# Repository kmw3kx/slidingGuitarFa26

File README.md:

# slidingGuitarFa26
Repo for all of the electronics &amp; code for my Fa26 capstone group 

## Daisy Pins

## Basic idea

6 string guitar with glass slider attached to linear actuator.

From gemini:

$$\text{Total Encoder Positions} = \frac{575\text{ mm}}{0.1894\text{ mm/count}} \approx \mathbf{3,036\text{ discrete positions}}$$

My original idea was to use pitchbend midi control for slider position, but it doesn't appear to be completely necessary. But it will fit for now.

Then I will use a cc channel or 2 for the gains on the Op-amps

I will build this demo in puredata so that I can start composing for it.

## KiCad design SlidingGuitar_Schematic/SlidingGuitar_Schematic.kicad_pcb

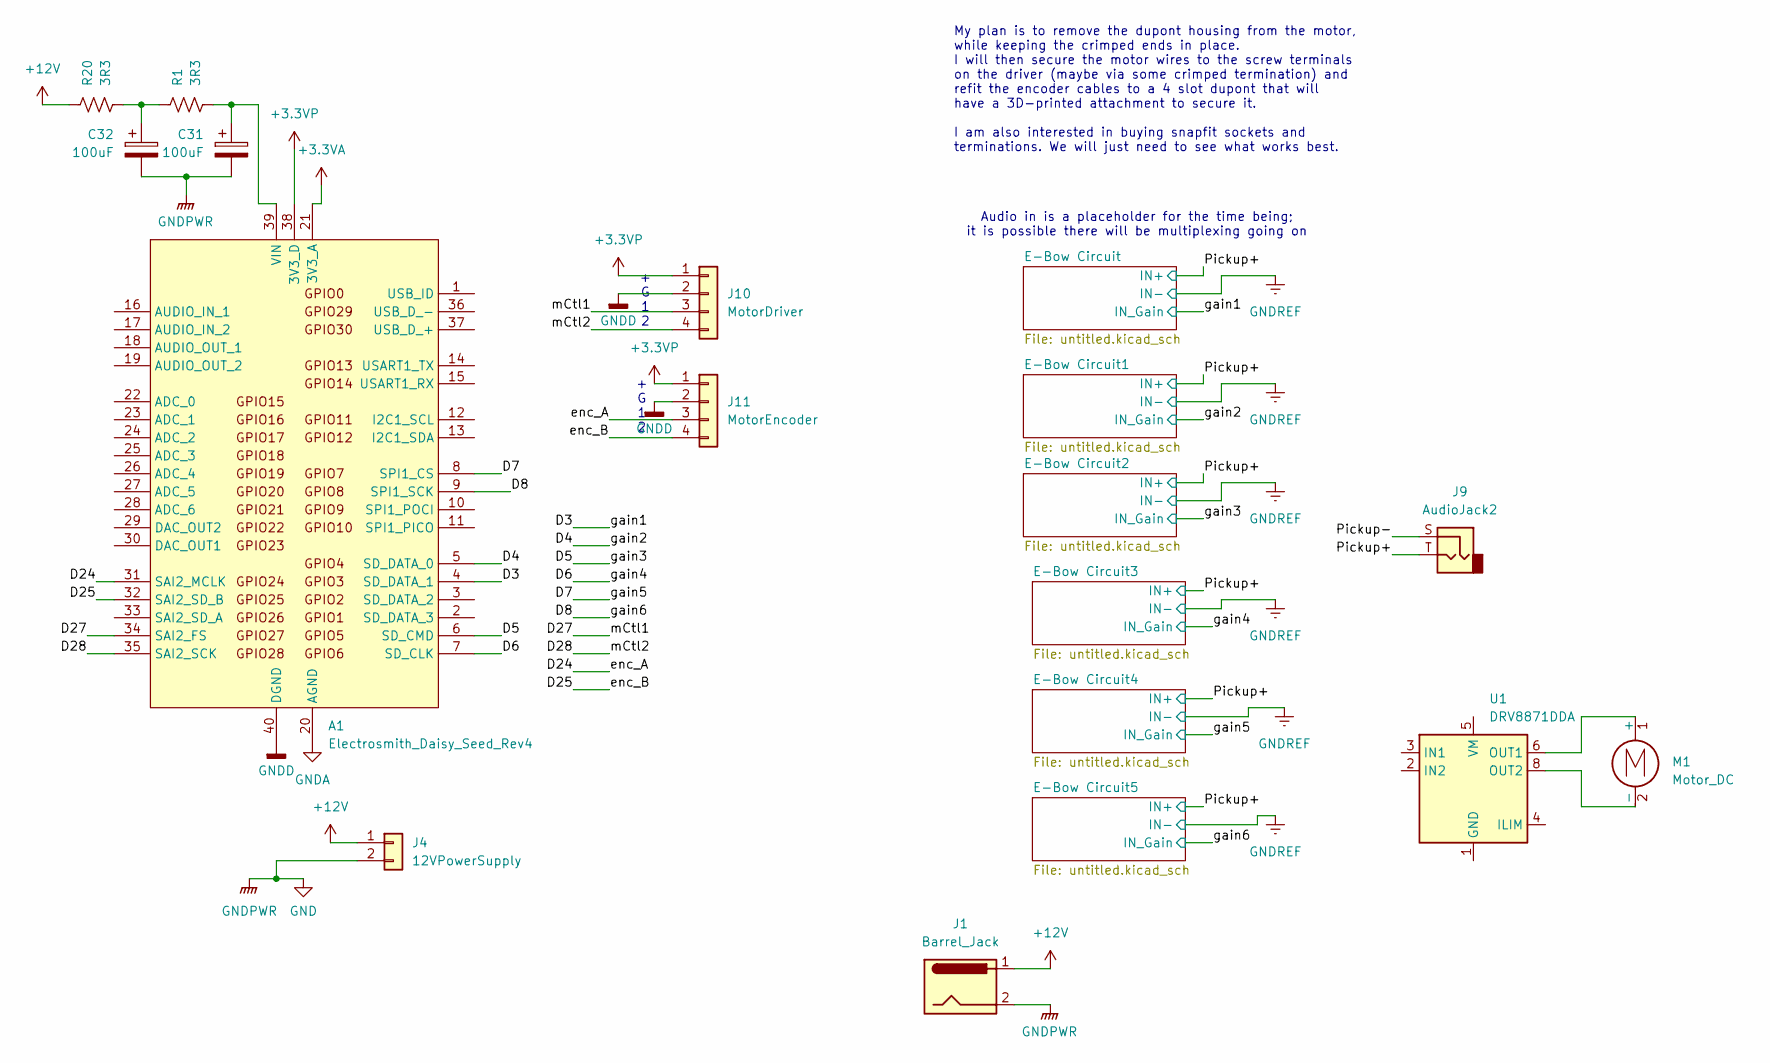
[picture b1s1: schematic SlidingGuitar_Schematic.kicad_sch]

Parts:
A1: Electrosmith_Daisy_Seed_Rev4; Electrosmith_Daisy_Seed
C31, C32: 100uF; CP_Radial_D8.0mm_P5.00mm
J1: Barrel_Jack; BarrelJack_Horizontal
J4: 12VPowerSupply; PinHeader_1x02_P2.54mm_Vertical
J9: AudioJack2
J10: MotorDriver; PinHeader_1x04_P2.54mm_Vertical
J11: MotorEncoder; PinHeader_1x04_P2.54mm_Vertical
M1: Motor_DC
R1, R20: 3R3; R_Axial_DIN0207_L6.3mm_D2.5mm_P7.62mm_Horizontal
U1: DRV8871DDA; Texas_HTSOP-8-1EP_3.9x4.9mm_P1.27mm_EP2.95x4.9mm_Mask2.4x3.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

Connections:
+3.3VA: A1.21 (3V3_A)
+3.3VP: A1.38 (3V3_D), J10.1, J11.1
+12V: J1.1, J4.1, R20.1; also elsewhere on the board
/D3: A1.4 (SD_DATA_1); also elsewhere on the board
/D4: A1.5 (SD_DATA_0); also elsewhere on the board
/D5: A1.6 (SD_CMD); also elsewhere on the board
/D6: A1.7 (SD_CLK); also elsewhere on the board
/D7: A1.8 (SPI1_CS); also elsewhere on the board
/D8: A1.9 (SPI1_SCK); also elsewhere on the board
/D24: A1.31 (SAI2_MCLK), J11.3
/D25: A1.32 (SAI2_SD_B), J11.4
/D27: A1.34 (SAI2_FS), J10.3
/D28: A1.35 (SAI2_SCK), J10.4
GND: C31.2, C32.2, J1.2, J4.2; also elsewhere on the board
GNDA: A1.20 (AGND)
GNDD: A1.40 (DGND), J10.2, J11.2; also elsewhere on the board
unnamed: A1.39 (VIN), C31.1, R1.2
unnamed: C32.1, R1.1, R20.2
unnamed: M1.1 (+), U1.6 (OUT1)
unnamed: M1.2 (-), U1.8 (OUT2)
unnamed: U1.1 (GND), U1.7 (GND), U1.9 (GND)

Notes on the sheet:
+ G 1 2
Audio in is a placeholder for the time being; it is possible there will be multiplexing going on
My plan is to remove the dupont housing from the motor, while keeping the crimped ends in place. I will then secure the motor wires to the screw terminals on the driver (maybe via some crimped termination) and refit the encoder cables to a 4 slot dupont that will have a 3D-printed attachment to sec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

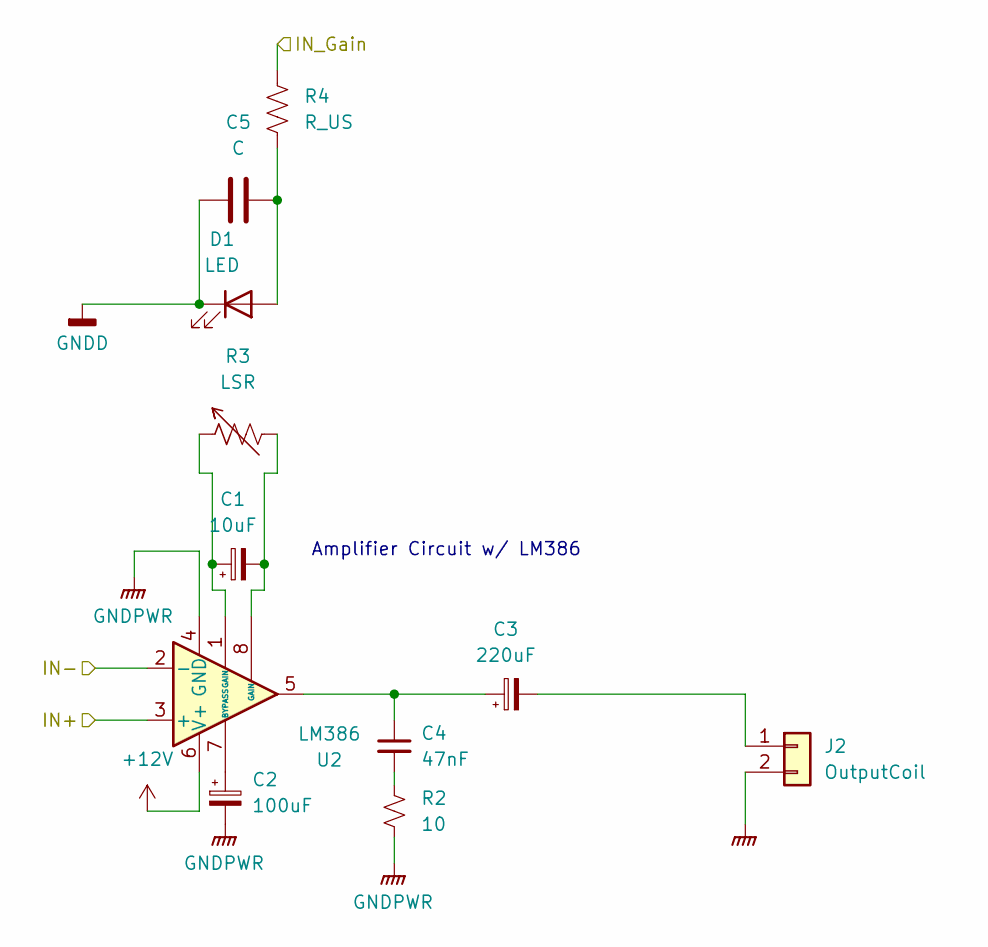
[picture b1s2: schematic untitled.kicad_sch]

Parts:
C1: 10uF; CP_Radial_D8.0mm_P5.00mm
C2: 100uF; CP_Radial_D8.0mm_P5.00mm
C3: 220uF; CP_Radial_D8.0mm_P5.00mm
C4: 47nF; C_Disc_D3.8mm_W2.6mm_P2.50mm
C5: C; PinSocket_1x02_P2.54mm_Vertical
D1: LED; LED_D5.0mm_Horizontal_O3.81mm_Z3.0mm
J2: OutputCoil; PinHeader_1x02_P2.54mm_Vertical
R2: 10; R_Axial_DIN0207_L6.3mm_D2.5mm_P7.62mm_Horizontal
R3: LSR; R_LDR_5.2x5.2mm_P3.5mm_Horizontal
R4: R_US; R_Axial_DIN0207_L6.3mm_D2.5mm_P7.62mm_Horizontal
U2: LM386; DIP-8_W7.62mm

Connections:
+12V: U2.6 (V+); also elsewhere on the board
/D3: R4.1; also elsewhere on the board
/Pickup+: U2.3 (+); also elsewhere on the board
GND: C2.2, J2.2, R2.2, U2.4 (GND); also elsewhere on the board
GNDD: C5.1, D1.1 (K); also elsewhere on the board
GNDREF: U2.2 (-); also elsewhere on the board
unnamed: C1.1, R3.1, U2.1 (GAIN)
unnamed: C1.2, R3.2, U2.8 (GAIN)
unnamed: C3.1, C4.1, U2.5
unnamed: C4.2, R2.1
unnamed: C5.2, D1.2 (A), R4.2
unnamed: C3.2, J2.1
unnamed: C2.1, U2.7 (BYPASS)

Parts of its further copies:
C6, C11, C16, C21, C26: 100uF; CP_Radial_D8.0mm_P5.00mm
C7, C12, C17, C22, C27: C; PinSocket_1x02_P2.54mm_Vertical
C8, C13, C18, C23, C28: 10uF; CP_Radial_D8.0mm_P5.00mm
C9, C14, C19, C24, C29: 47nF; C_Disc_D3.8mm_W2.6mm_P2.50mm
C10, C15, C20, C25, C30: 220uF; CP_Radial_D8.0mm_P5.00mm
D2, D3, D4, D5, D6: LED; LED_D5.0mm_Horizontal_O3.81mm_Z3.0mm
J3, J5, J6, J7, J8: OutputCoil; PinHeader_1x02_P2.54mm_Vertical
R5, R8, R11, R14, R17: LSR; R_LDR_5.2x5.2mm_P3.5mm_Horizontal
R6, R9, R12, R15, R18: R_US; R_Axial_DIN0207_L6.3mm_D2.5mm_P7.62mm_Horizontal
R7, R10, R13, R16, R19: 10; R_Axial_DIN0207_L6.3mm_D2.5mm_P7.62mm_Horizontal
U3, U4, U5, U6, U7: LM386; DIP-8_W7.62mm

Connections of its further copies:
+12V: U3.6 (V+), U4.6 (V+), U5.6 (V+), U6.6 (V+), U7.6 (V+); also elsewhere on the board
/D4: R6.1; also elsewhere on the board
/D5: R9.1; also elsewhere on the board
/D6: R12.1; also elsewhere on the board
/D7: R15.1; also elsewhere on the board
/D8: R18.1; also elsewhere on the board
/Pickup+: U3.3 (+), U4.3 (+), U5.3 (+), U6.3 (+), U7.3 (+); also elsewhere on the board
GND: C6.2, C11.2, C16.2, C21.2, C26.2, J3.2, J5.2, J6.2, J7.2, J8.2, R7.2, R10.2, R13.2, R16.2, R19.2, U3.4 (GND), U4.4 (GND), U5.4 (GND), U6.4 (GND), U7.4 (GND); also elsewhere on the board
GNDD: C7.1, C12.1, C17.1, C22.1, C27.1, D2.1 (K), D3.1 (K), D4.1 (K), D5.1 (K), D6.1 (K); also elsewhere on the board
GNDREF: U3.2 (-), U4.2 (-), U5.2 (-), U6.2 (-), U7.2 (-); also elsewhere on the board
unnamed: C8.1, R5.1, U3.1 (GAIN)
unnamed: C8.2, R5.2, U3.8 (GAIN)
unnamed: C9.2, R7.1
unnamed: C9.1, C10.1, U3.5
unnamed: C13.1, R8.1, U4.1 (GAIN)
unnamed: C13.2, R8.2, U4.8 (GAIN)
unnamed: C14.1, C15.1, U4.5
unnamed: C14.2, R10.1
unnamed: C18.1, R11.1, U5.1 (GAIN)
unnamed: C18.2, R11.2, U5.8 (GAIN)
unnamed: C19.1, C20.1, U5.5
unnamed: C19.2, R13.1
unnamed: C23.1, R14.1, U6.1 (GAIN)
unnamed: C23.2, R14.2, U6.8 (GAIN)
unnamed: C24.1, C25.1, U6.5
unnamed: C24.2, R16.1
unnamed: C28.1, R17.1, U7.1 (GAIN)
unnamed: C28.2, R17.2, U7.8 (GAIN)
unnamed: C29.1, C30.1, U7.5
unnamed: C29.2, R19.1
unnamed: C7.2, D2.2 (A), R6.2
unnamed: C12.2, D3.2 (A), R9.2
unnamed: C17.2, D4.2 (A), R12.2
unnamed: C22.2, D5.2 (A), R15.2
unnamed: C27.2, D6.2 (A), R18.2
unnamed: C10.2, J3.1
unnamed: C15.2, J5.1
unnamed: C20.2, J6.1
unnamed: C25.2, J7.1
unnamed: C30.2, J8.1
unnamed: C6.1, U3.7 (BYPASS)
unnamed: C11.1, U4.7 (BYPASS)
unnamed: C16.1, U5.7 (BYPASS)
unnamed: C21.1, U6.7 (BYPASS)
unnamed: C26.1, U7.7 (BYPASS)

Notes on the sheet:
Amplifier Circuit w/ LM386

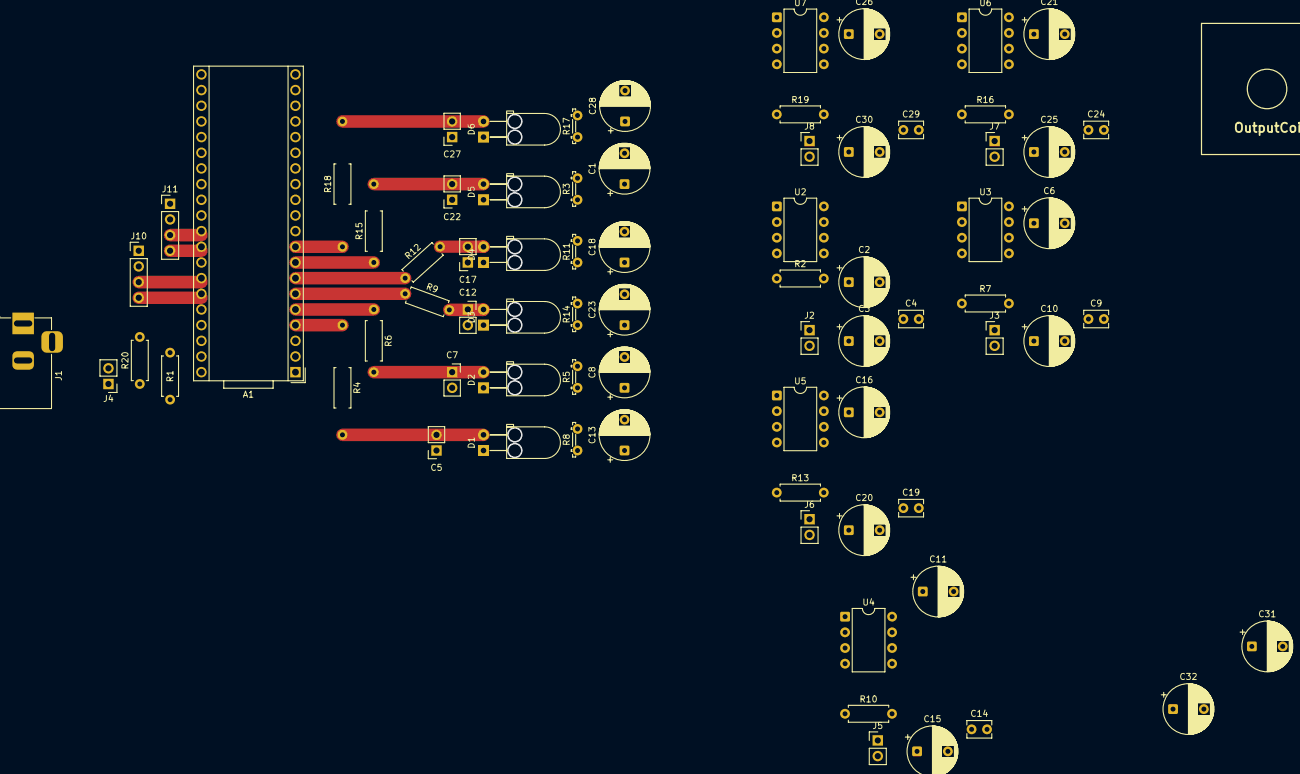
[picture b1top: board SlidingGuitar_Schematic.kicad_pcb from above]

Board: 2 copper layers, 75 parts (0 on the bottom side), 60 nets.
